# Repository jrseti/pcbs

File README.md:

# Printed Curcuit Board Projects

This repository contains various printed circuit board projects. Also includes any custom firmware where applicable.

## parts

This is a git submodule pointing to https://github.com/jrseti/parts.

The contains pcb related symbols, footprints and 3d files for KiCad PCB projects. All KiCAD projects in this repository will use parts that are in these libraries. 

During development if a part is not in this library, add it. See directions in the parts/READM.md file.

Make sure it is always updated to the latest:

- git submodule update --init --recursive

# mcu_test_board

This is a PCB project to create a board that has a STM32 MCU that runs a PID loop. Once this is debugged and working the design will be inproved in a more encompaing board.

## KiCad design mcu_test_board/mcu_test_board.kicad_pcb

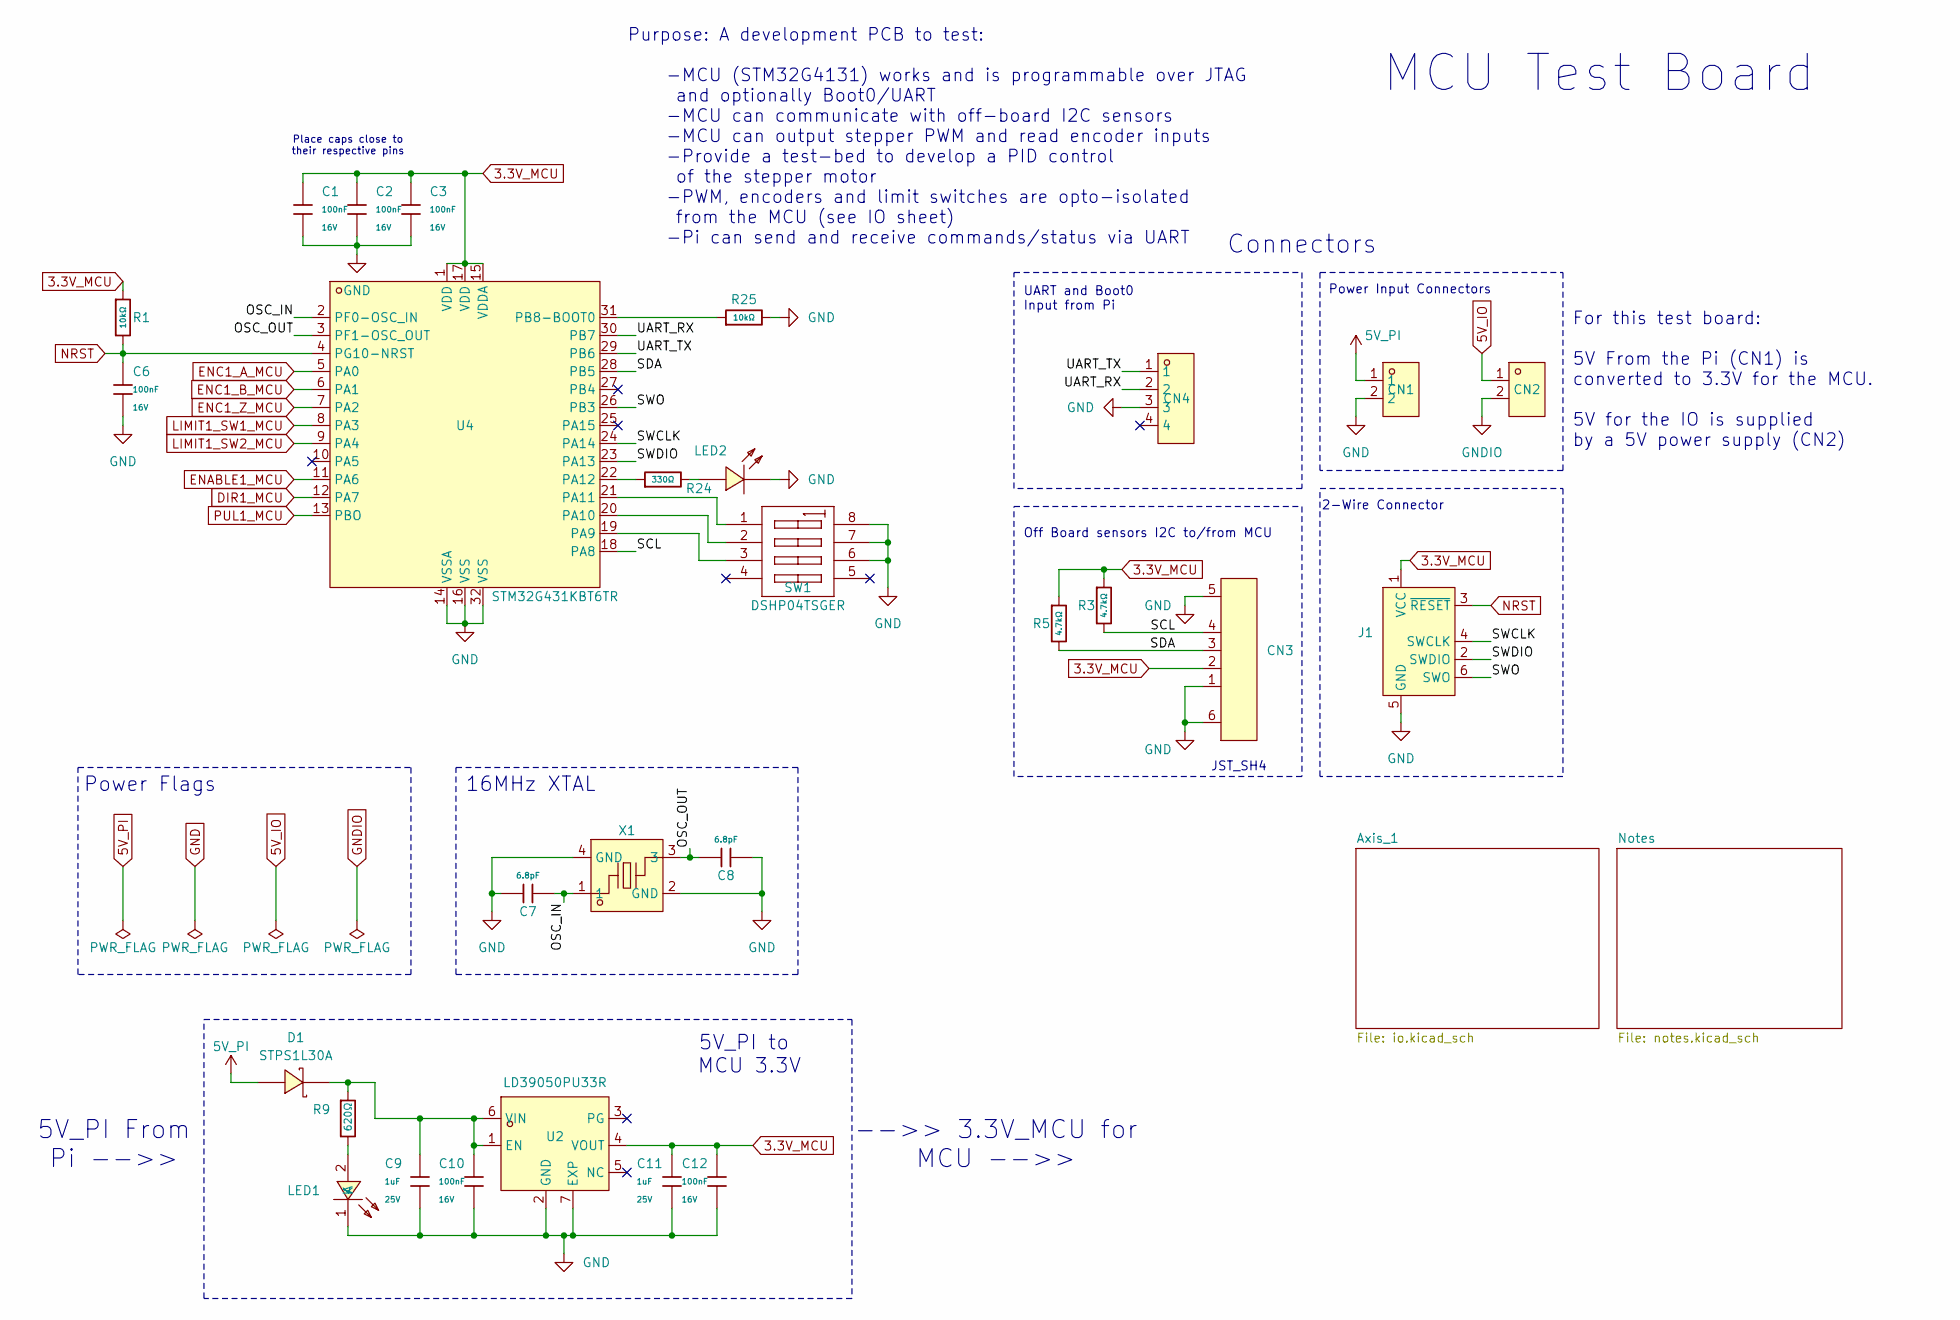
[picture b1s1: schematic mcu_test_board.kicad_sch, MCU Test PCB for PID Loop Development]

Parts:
C1, C2, C3, C6, C10, C12: 100nF; C_0402; Voltage Rated 16V; Tolerance ±10%; Part CL05B104KO5NNNC; LCSC C1525
C7, C8: 6.8pF; C_0402; Voltage Rated 50V; Part 0402CG6R8C500NT; LCSC C1576
C9, C11: 1uF; C_0402; Voltage Rated 25V; Tolerance ±10%; Part CL05A105KA5NQNC; LCSC C52923
CN1, CN2: KF2EDGR-2.54-2P; CONN-TH_P2.54_KF2EDGR-2.54-2P; LCSC Part C577594
CN3: SM04B-SRSS-TB (LF)(SN); CONN-SMD_4P-P1.00_SM04B-SRSS-TB-LF-SN; LCSC Part C160404
CN4: KF2EDGR-2.54-4P; CONN-TH_4P-P2.54_KF2EDGR-2.54-4P; LCSC Part C577596
D1: STPS1L30A; SMA_L4.3-W2.6-LS5.2-RD; LCSC Part C157388
J1: Conn_ARM_SWD_TagConnect_TC2030-NL; Tag-Connect_TC2030-IDC-NL_2x03_P1.27mm_Vertical
LED1, LED2: LTST-S270KGKT; LED-SMD_L1.7-W0.6-RD; LCSC Part C125113
R1, R25: 10kΩ; R_0402; Overload Voltage (Max) 50V; Tolerance ±1%; Part 0402WGF1002TCE; LCSC C25744
R3, R5: 4.7kΩ; R_0402; Overload Voltage (Max) 50V; Tolerance ±1%; Part 0402WGF4701TCE; LCSC C25900
R9: 620Ω; R_0603; Overload Voltage (Max) 75V; Tolerance ±1%; Part 0603WAF6200T5E; LCSC C23220
R24: 330Ω; R_0402; Overload Voltage (Max) 50V; Tolerance ±1%; Part 0402WGF3300TCE; LCSC C25104
SW1: DSHP04TSGER; SW-SMD_8P-L6.7-W5.4-P1.27-LS8.4; LCSC Part C40736
U2: LD39050PU33R; DFN-6_L3.0-W3.0-P0.95-LS3.1-TL-EP; LCSC Part C132827
U4: STM32G431KBT6TR; LQFP-32_L7.0-W7.0-P0.80-LS9.0-BL; LCSC Part C5270317
X1: NX2016SA-16MHZ-EXS00A-CS07826; CRYSTAL-SMD_4P-L2.0-W1.6-BL; LCSC Part C7322371

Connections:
3.3V_MCU: C1.1, C2.1, C3.1, C11.1, C12.1, CN3.2, J1.1 (VCC), R1.1, R3.1, R5.1, U2.4 (VOUT), U4.1 (VDD), U4.15 (VDDA), U4.17 (VDD); also elsewhere on the board
5V_IO: CN2.1; also elsewhere on the board
5V_PI: CN1.1, D1.2 (A)
/OSC_IN: C7.2, U4.2 (PF0-OSC_IN), X1.1
/OSC_OUT: C8.1, U4.3 (PF1-OSC_OUT), X1.3
/SCL: CN3.4, R3.2, U4.18 (PA8)
/SDA: CN3.3, R5.2, U4.28 (PB5)
/SWCLK: J1.4 (SWCLK), U4.24 (PA14)
/SWDIO: J1.2 (SWDIO), U4.23 (PA13)
/SWO: J1.6 (SWO), U4.26 (PB3)
/UART_RX: CN4.2, U4.30 (PB7)
/UART_TX: CN4.1, U4.29 (PB6)
DIR1_MCU: U4.12 (PA7); also elsewhere on the board
ENABLE1_MCU: U4.11 (PA6); also elsewhere on the board
ENC1_A_MCU: U4.5 (PA0); also elsewhere on the board
ENC1_B_MCU: U4.6 (PA1); also elsewhere on the board
ENC1_Z_MCU: U4.7 (PA2); also elsewhere on the board
GND: C1.2, C2.2, C3.2, C6.2, C7.1, C8.2, C9.2, C10.2, C11.2, C12.2, CN1.2, CN3.1, CN3.5, CN3.6, CN4.3, J1.5 (GND), LED1.1 (K), LED2.1 (K), R25.2, SW1.6 (B3), SW1.7 (B2), SW1.8 (B1), U2.2 (GND), U2.7 (EXP), U4.14 (VSSA), U4.16 (VSS), U4.32 (VSS), X1.2 (GND), X1.4 (GND); also elsewhere on the board
GNDIO: CN2.2; also elsewhere on the board
LIMIT1_SW1_MCU: U4.8 (PA3); also elsewhere on the board
LIMIT1_SW2_MCU: U4.9 (PA4); also elsewhere on the board
NRST: C6.1, J1.3 (~RESET), R1.2, U4.4 (PG10-NRST)
unnamed: C9.1, C10.1, D1.1 (C), R9.1, U2.1 (EN), U2.6 (VIN)
unnamed: LED1.2 (A), R9.2
unnamed: LED2.2 (A), R24.2
unnamed: SW1.1 (A1), U4.21 (PA11)
unnamed: SW1.2 (A2), U4.20 (PA10)
unnamed: SW1.3 (A3), U4.19 (PA9)
unnamed: R24.1, U4.22 (PA12)
unnamed: R25.1, U4.31 (PB8-BOOT0)
PUL1_MCU: U4.13 (PBO); also elsewhere on the board

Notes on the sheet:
2-Wire Connector
16MHz XTAL
Off Board sensors I2C to/from MCU
Connectors
JST_SH4
Power Input Connectors
UART and Boot0 Input from Pi
For this test board: 5V From the Pi (CN1) is converted to 3.3V for the MCU. 5V for the IO is supplied by a 5V power supply (CN2)
Place caps close to their respective pins
Power Flags
-->> 3.3V_MCU for MCU -->>
MCU Test Board
Purpose: A development PCB to test: -MCU (STM32G4131) works and is programmable over JTAG and optionally Boot0/UART -MCU can communicate with off-board I2C sensors -MCU can output stepper PWM and read encoder inputs -Provide a test-bed to develop a PID control of the stepper motor -PWM, encoders an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
5V_PI to MCU 3.3V
5V_PI From Pi -->>

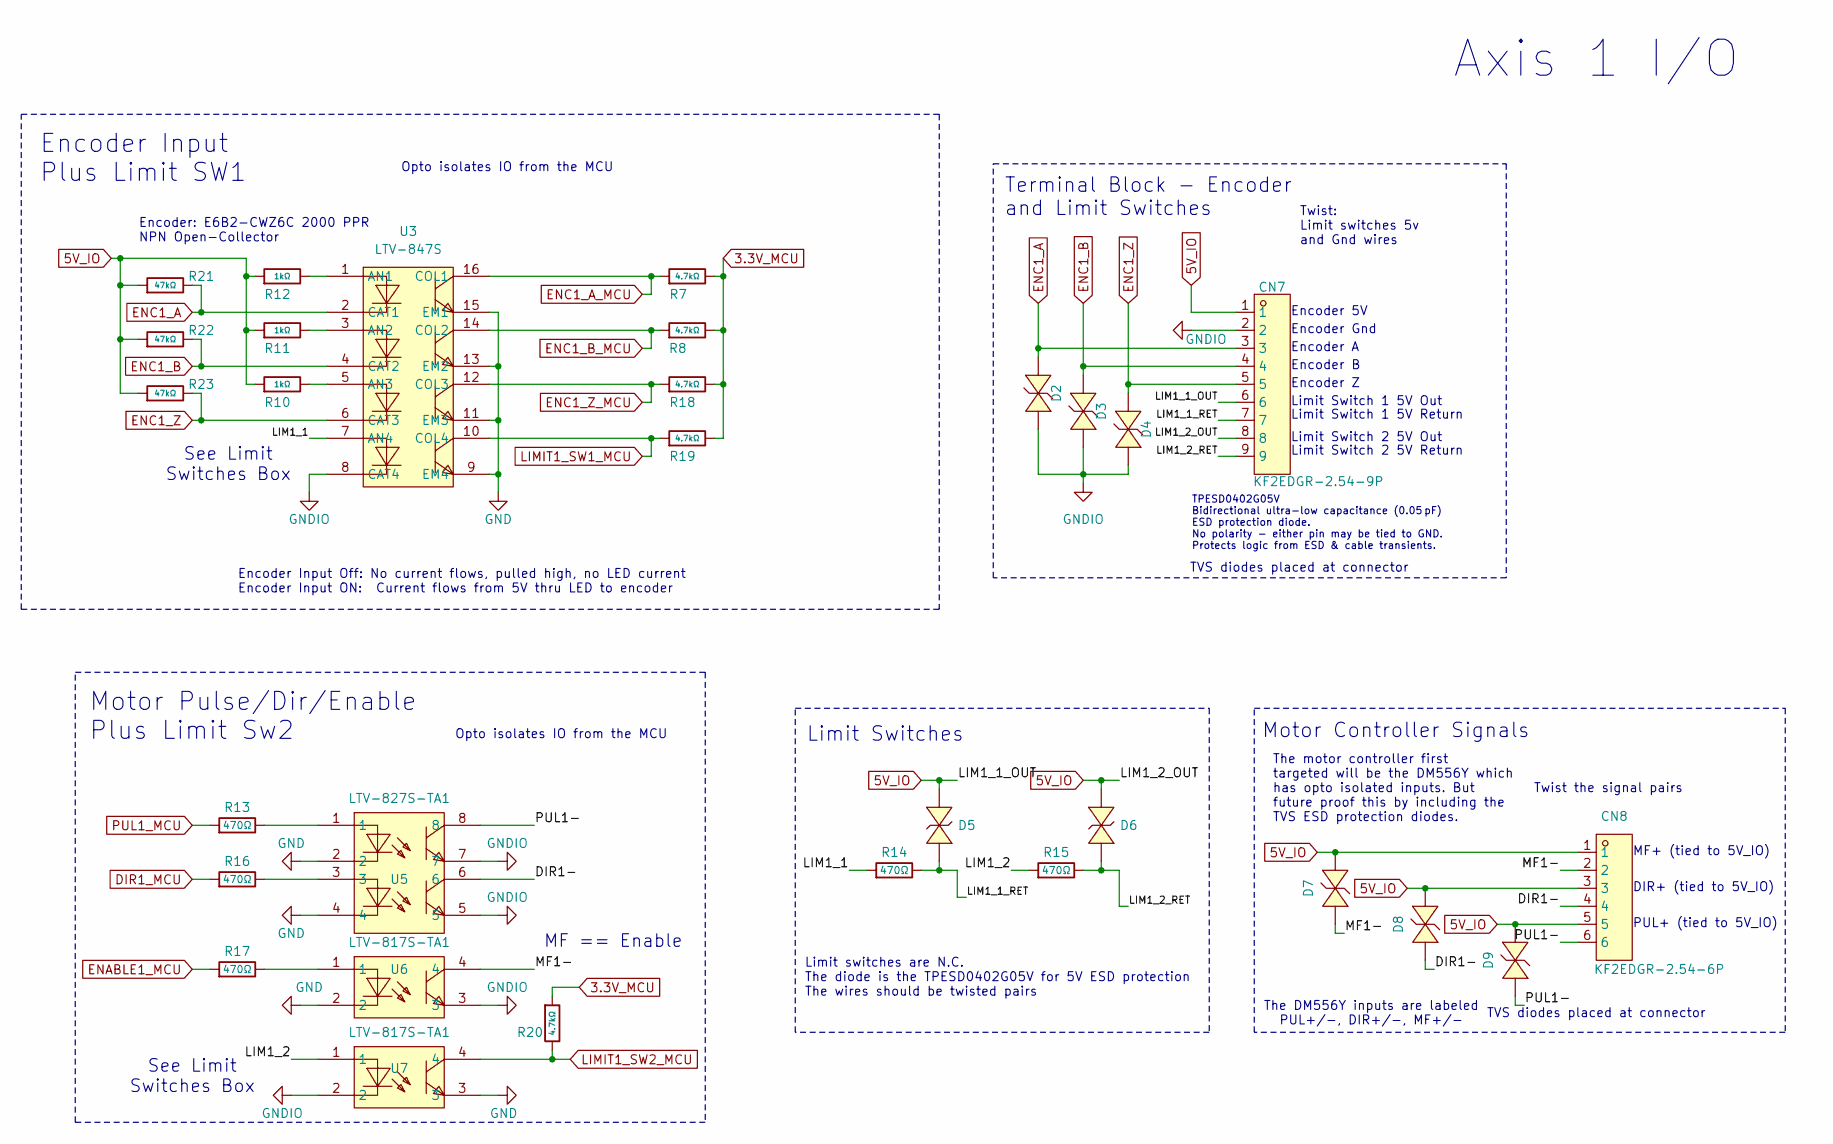
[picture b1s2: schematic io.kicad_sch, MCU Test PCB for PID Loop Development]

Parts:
CN7: KF2EDGR-2.54-9P; CONN-TH_9P-P2.54_KF2EDGR-2.54-9P; LCSC Part C577601
CN8: KF2EDGR-2.54-6P; CONN-TH_KF2EDGR-2.54-6P; LCSC Part C577598
D2, D3, D4, D7, D8, D9: TPESD0402G05V; D0402-BI; LCSC Part C558615
D5, D6: TPESD0402G05V; D0402-BI; LCSC Part C558617
R7, R8, R18, R19, R20: 4.7kΩ; R_0603; Overload Voltage (Max) 75V; Tolerance ±1%; Part 0603WAF4701T5E; LCSC C23162
R10, R11, R12: 1kΩ; R_0402; Overload Voltage (Max) 50V; Tolerance ±1%; Part 0402WGF1001TCE; LCSC C11702
R13, R14, R15, R16, R17: 470Ω; R_0402; Overload Voltage (Max) 50V; Tolerance ±1%; Part 0402WGF4700TCE; LCSC C25117
R21, R22, R23: 47kΩ; R_0402; Overload Voltage (Max) 50V; Tolerance ±1%; Part 0402WGF4702TCE; LCSC C25792
U3: LTV-847S; SMD-16_L20.0-W6.5-P2.54-LS10.2-BL; LCSC Part C114599
U5: LTV-827S-TA1; SMD-8_L9.8-W6.6-P2.54-LS10.3-BL; LCSC Part C22112
U6, U7: LTV-817S-TA1; OPTO-SMD-4_L4.6-W6.5-P2.54-LS10.3-BL; LCSC Part C125121

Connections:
3.3V_MCU: R7.2, R8.2, R18.2, R19.2, R20.1; also elsewhere on the board
5V_IO: CN7.1, CN7.6, CN7.8, CN8.1, CN8.3, CN8.5, D5.1, D6.1, D7.1 (K), D8.1 (K), D9.1 (K), R10.1, R11.1, R12.1, R21.1, R22.1, R23.1; also elsewhere on the board
/Axis_1/DIR1-: CN8.4, D8.2 (A), U5.6
/Axis_1/LIM1_1: R14.1, U3.7 (AN4)
/Axis_1/LIM1_1_RET: CN7.7, D5.2, R14.2
/Axis_1/LIM1_2: R15.1, U7.1
/Axis_1/LIM1_2_RET: CN7.9, D6.2, R15.2
/Axis_1/MF1-: CN8.2, D7.2 (A), U6.4
/Axis_1/PUL1-: CN8.6, D9.2 (A), U5.8
DIR1_MCU: R16.1; also elsewhere on the board
ENABLE1_MCU: R17.1; also elsewhere on the board
ENC1_A: CN7.3, D2.1 (K), R21.2, U3.2 (CAT1)
ENC1_A_MCU: R7.1, U3.16 (COL1); also elsewhere on the board
ENC1_B: CN7.4, D3.1 (K), R22.2, U3.4 (CAT2)
ENC1_B_MCU: R8.1, U3.14 (COL2); also elsewhere on the board
ENC1_Z: CN7.5, D4.1 (K), R23.2, U3.6 (CAT3)
ENC1_Z_MCU: R18.1, U3.12 (COL3); also elsewhere on the board
GND: U3.9 (EM4), U3.11 (EM3), U3.13 (EM2), U3.15 (EM1), U5.2, U5.4, U6.2, U7.3; also elsewhere on the board
GNDIO: CN7.2, D2.2 (A), D3.2 (A), D4.2 (A), U3.8 (CAT4), U5.5, U5.7, U6.3, U7.2; also elsewhere on the board
LIMIT1_SW1_MCU: R19.1, U3.10 (COL4); also elsewhere on the board
LIMIT1_SW2_MCU: R20.2, U7.4; also elsewhere on the board
unnamed: R13.2, U5.1
unnamed: R16.2, U5.3
unnamed: R17.2, U6.1
unnamed: R12.2, U3.1 (AN1)
unnamed: R11.2, U3.3 (AN2)
unnamed: R10.2, U3.5 (AN3)
PUL1_MCU: R13.1; also elsewhere on the board

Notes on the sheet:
Limit Switch 2 5V Return
Encoder A
Limit switches are N.C. The diode is the TPESD0402G05V for 5V ESD protection The wires should be twisted pairs
PUL+ (tied to 5V_IO)
Opto isolates IO from the MCU
Encoder 5V
Motor Pulse/Dir/Enable Plus Limit Sw2
See Limit Switches Box
Encoder: E6B2-CWZ6C 2000 PPR NPN Open-Collector
Opto isolates IO from the MCU
Encoder Gnd
Axis 1 I/O
Twist: Limit switches 5v and Gnd wires
TPESD0402G05V Bidirectional ultra-low capacitance (0.05 pF) ESD protection diode. No polarity - either pin may be tied to GND. Protects logic from ESD & cable transients.
Limit Switch 2 5V Out
Encoder Input Off: No current flows, pulled high, no LED current Encoder Input ON: Current flows from 5V thru LED to encoder
TVS diodes placed at connector
MF+ (tied to 5V_IO)
Limit Switch 1 5V Return
Terminal Block - Encoder and Limit Switches
The DM556Y inputs are labeled PUL+/-, DIR+/-, MF+/-
Encoder Input Plus Limit SW1
Limit Switches
Motor Controller Signals
Encoder Z
DIR+ (tied to 5V_IO)
The motor controller first targeted will be the DM556Y which has opto isolated inputs. But future proof this by including the TVS ESD protection diodes.
Twist the signal pairs
MF == Enable
Limit Switch 1 5V Out
Encoder B

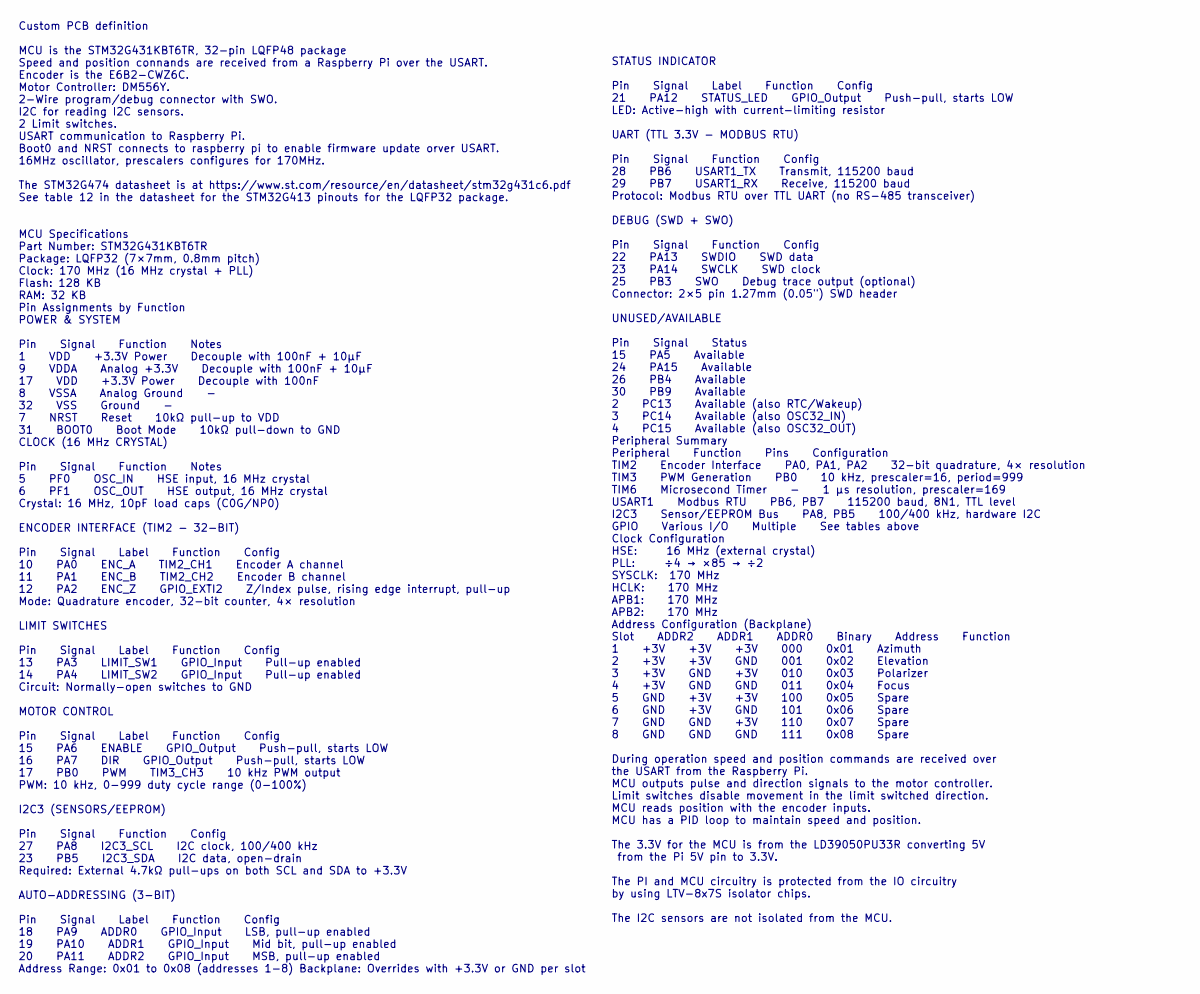
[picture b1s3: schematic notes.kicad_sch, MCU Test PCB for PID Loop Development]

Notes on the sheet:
STATUS INDICATOR Pin Signal Label Function Config 21 PA12 STATUS_LED GPIO_Output Push-pull, starts LOW LED: Active-high with current-limiting resistor UART (TTL 3.3V - MODBUS RTU) Pin Signal Function Config 28 PB6 USART1_TX Transmit, 115200 baud 29 PB7 USART1_RX Receive, 115200 baud Protocol: Modbu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
Custom PCB definition MCU is the STM32G431KBT6TR, 32-pin LQFP48 package Speed and position connands are received from a Raspberry Pi over the USART. Encoder is the E6B2-CWZ6C. Motor Controller: DM556Y. 2-Wire program/debug connector with SWO. I2C for reading I2C sensors. 2 Limit switches. USART com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

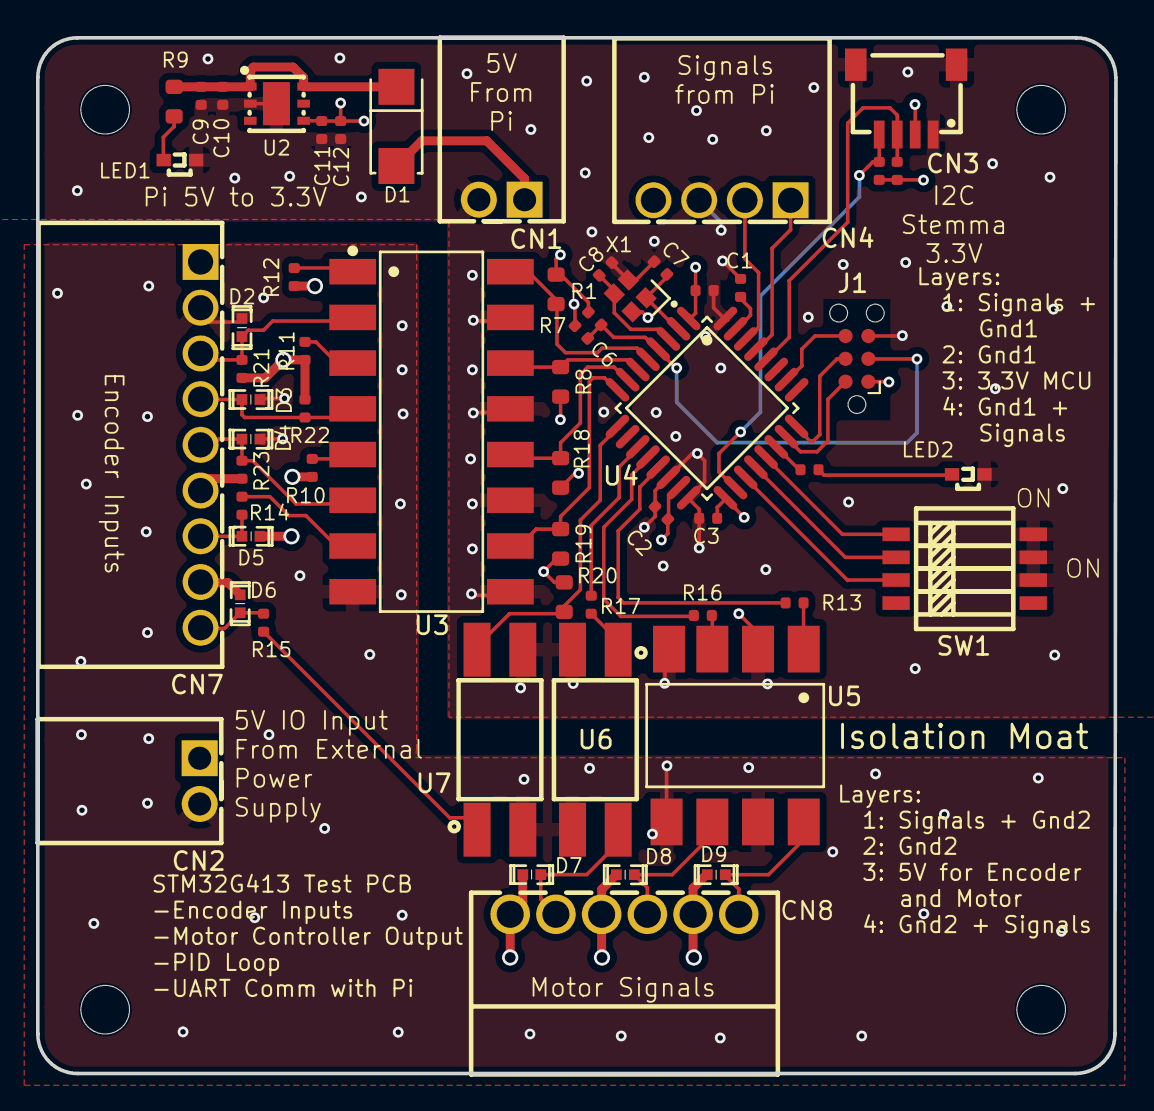
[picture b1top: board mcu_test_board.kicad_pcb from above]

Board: 4 copper layers, 59.9 x 57.5 mm, 62 parts (0 on the bottom side), 47 nets.

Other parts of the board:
M1, M1#2, M1#3, M1#4: MountingHole_2.7mm_M2.5_ISO14580

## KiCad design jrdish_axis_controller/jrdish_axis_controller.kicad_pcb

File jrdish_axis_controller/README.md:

# Axis Controller

This PCB is an improved version of the mcu_test_board PCB. RS485, better isolation, fan power output and mode.

## Overview

This board follows on from the mcu_test_board. The mcu_test_board functions well, but quickly necessary improvements became evident to be able to fully service one axis of the satellite dish.

- PWM output. Isolated.
- Encoder inputs. Isolated.
- MCU will execute a PID loop.
- Upgrade to the STM32G473CET6 LQFP48. Has 512KB Flash vs 128KB.
- RS485. Isolated. With passthrough.
- MCU controllerd 12V output for fan on/off. Isolated.
- Requires only 12V input
- I2C isolation
- Onboard I2C temperature/humidity sensor. Not isolated.
- EEPROM.

## MCU

STM32G474CET6

- 512KB flash
- As of April 9, 2026 JLCPCB has 1152 in stock
- 48 pin
- JLCPCB Part # C730125 - https://jlcpcb.com/partdetail/STMicroelectronics-STM32G474CET6/C730125
- Datasheet: https://www.lcsc.com/datasheet/C730125.pdf

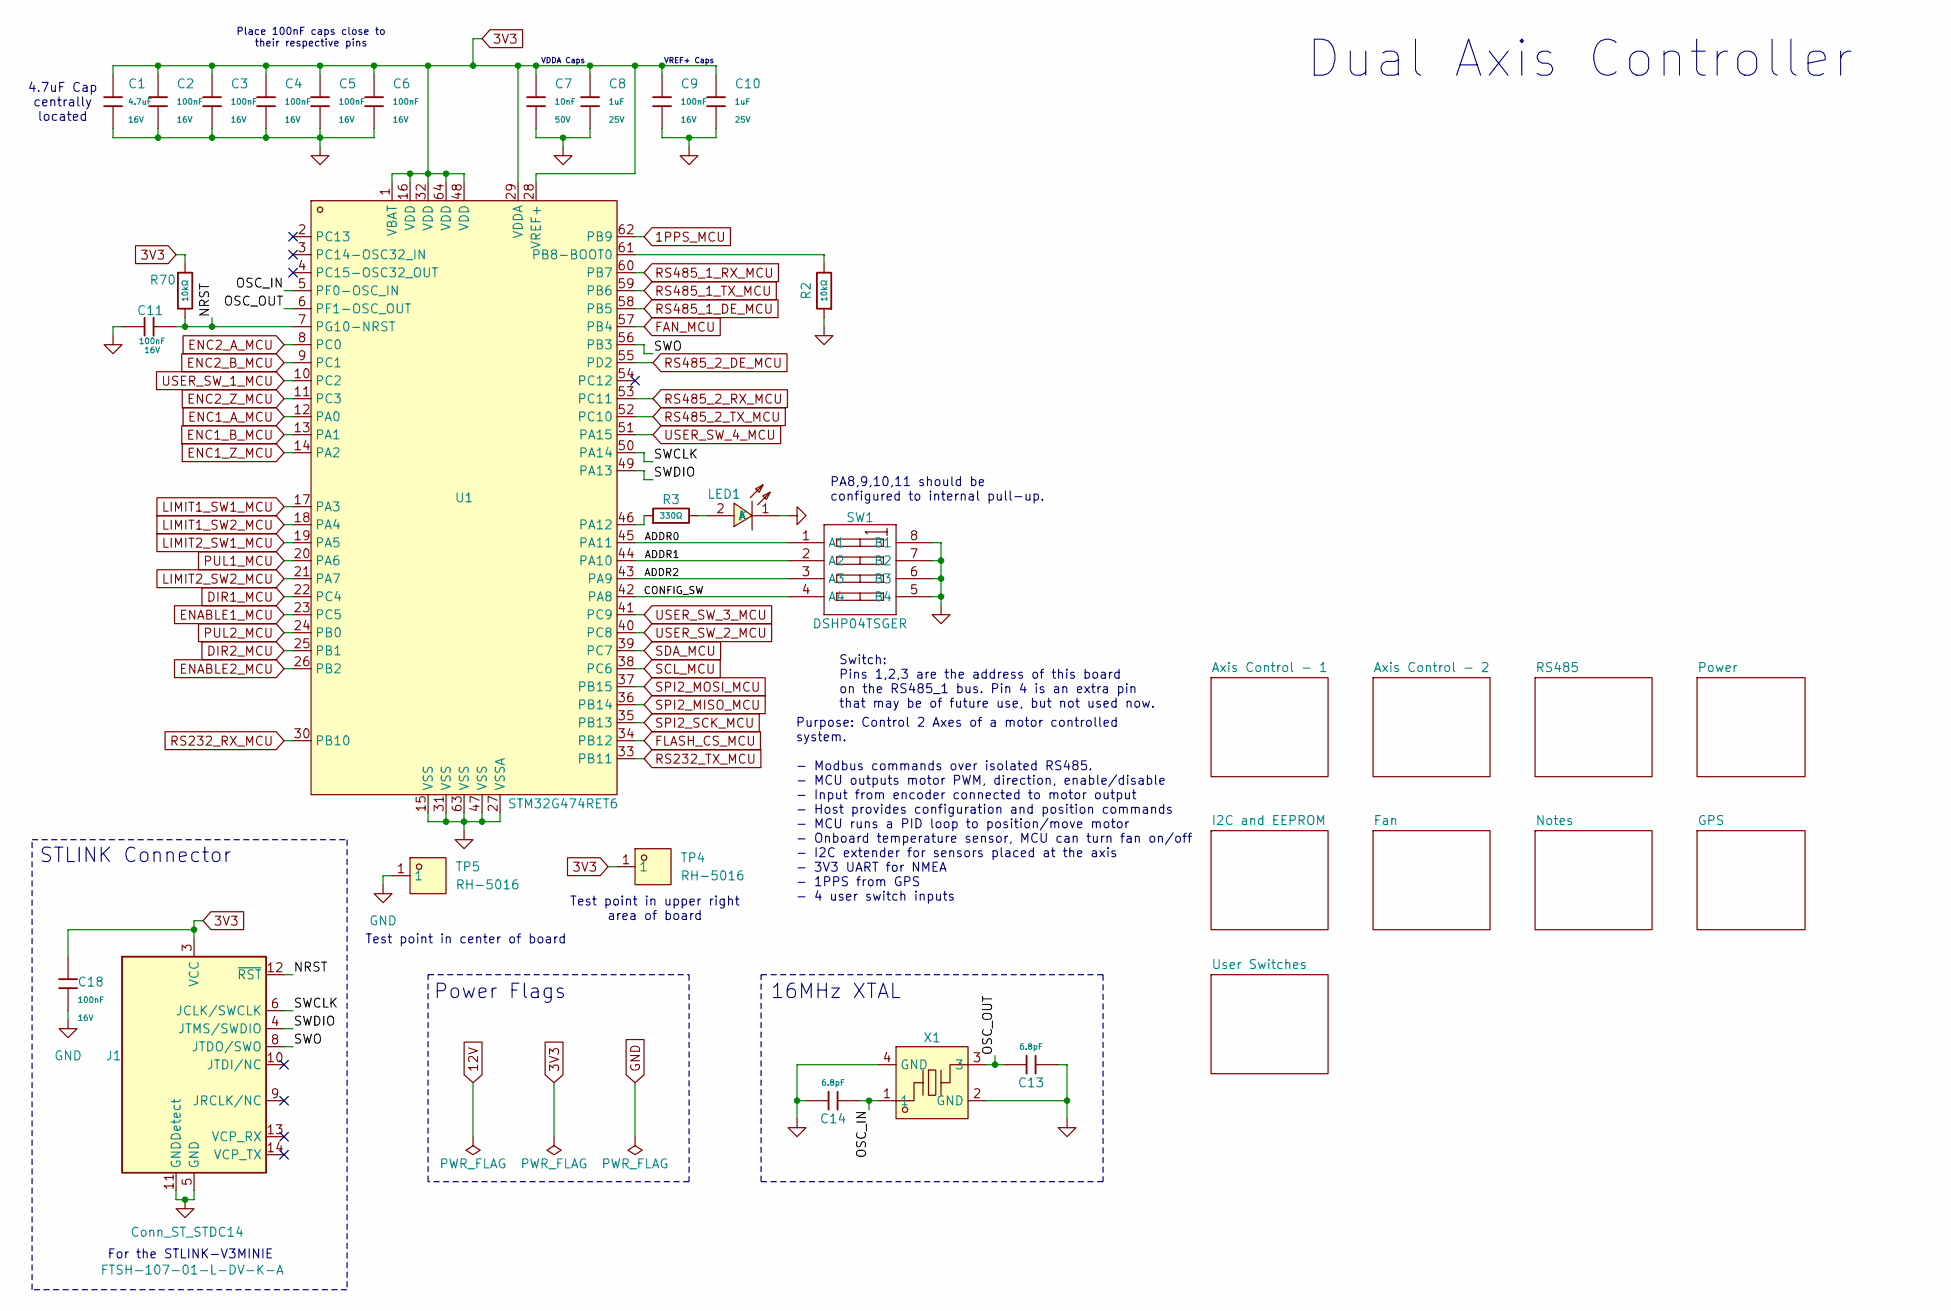
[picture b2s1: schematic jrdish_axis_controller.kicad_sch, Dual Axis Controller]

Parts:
C1: 4.7uF; C_0603; Voltage Rated 16V; Tolerance ±10%; Part CL10A475KO8NNNC; LCSC C19666
C2, C3, C4, C5, C6, C9, C11, C18: 100nF; C_0402; Voltage Rated 16V; Tolerance ±10%; Part CL05B104KO5NNNC; LCSC C1525
C7: 10nF; C_0402; Voltage Rated 50V; Tolerance ±10%; Part CL05B103KB5NNNC; LCSC C15195
C8, C10: 1uF; C_0402; Voltage Rated 25V; Tolerance ±10%; Part CL05A105KA5NQNC; LCSC C52923
C13, C14: 6.8pF; C_0402; Voltage Rated 50V; Part 0402CG6R8C500NT; LCSC C1576
J1: Conn_ST_STDC14; HDR-SMD_14P-P1.27_FTSH-107-01-L-DV-K; LCSC C5563894
LED1: LTST-S270KGKT; LED-SMD_L1.7-W0.6-RD; LCSC Part C125113
R2, R70: 10kΩ; R_0402; Overload Voltage (Max) 50V; Tolerance ±1%; Part 0402WGF1002TCE; LCSC C173683
R3: 330Ω; R_0402; Overload Voltage (Max) 50V; Tolerance ±1%; Part 0402WGF3300TCE; LCSC C25104
SW1: DSHP04TSGER; SW-SMD_8P-L6.7-W5.4-P1.27-LS8.4; LCSC Part C40736
TP4, TP5: RH-5016; TESTPOINT-SMD_L3.0-W2.0; MPN RH-5016; LCSC Part C5199799
U1: STM32G474RET6; LQFP-64_L10.0-W10.0-P0.50-LS12.0-BL; MPN STM32G474RET6; LCSC Part C521608
X1: NX2016SA-16MHZ-EXS00A-CS07826; CRYSTAL-SMD_4P-L2.0-W1.6-BL; LCSC Part C7322371

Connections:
1PPS_MCU: U1.62 (PB9); also elsewhere on the board
/ADDR0: SW1.1 (A1), U1.45 (PA11)
/ADDR1: SW1.2 (A2), U1.44 (PA10)
/ADDR2: SW1.3 (A3), U1.43 (PA9)
/CONFIG_SW: SW1.4 (A4), U1.42 (PA8)
/NRST: C11.1, J1.12 (~RST), R70.2, U1.7 (PG10-NRST)
/OSC_IN: C14.2, U1.5 (PF0-OSC_IN), X1.1
/OSC_OUT: C13.1, U1.6 (PF1-OSC_OUT), X1.3
/SWCLK: J1.6 (JCLK/SWCLK), U1.50 (PA14)
/SWDIO: J1.4 (JTMS/SWDIO), U1.49 (PA13)
/SWO: J1.8 (JTDO/SWO), U1.56 (PB3)
DIR1_MCU: U1.22 (PC4); also elsewhere on the board
DIR2_MCU: U1.25 (PB1); also elsewhere on the board
ENABLE1_MCU: U1.23 (PC5); also elsewhere on the board
ENABLE2_MCU: U1.26 (PB2); also elsewhere on the board
ENC1_A_MCU: U1.12 (PA0); also elsewhere on the board
ENC1_B_MCU: U1.13 (PA1); also elsewhere on the board
ENC1_Z_MCU: U1.14 (PA2); also elsewhere on the board
ENC2_A_MCU: U1.8 (PC0); also elsewhere on the board
ENC2_B_MCU: U1.9 (PC1); also elsewhere on the board
ENC2_Z_MCU: U1.11 (PC3); also elsewhere on the board
FAN_MCU: U1.57 (PB4); also elsewhere on the board
FLASH_CS_MCU: U1.34 (PB12); also elsewhere on the board
GND: C1.2, C2.2, C3.2, C4.2, C5.2, C6.2, C7.2, C8.2, C9.2, C10.2, C11.2, C13.2, C14.1, C18.2, J1.5 (GND), J1.7 (GND), J1.11 (GNDDetect), LED1.1 (K), R2.1, SW1.5 (B4), SW1.6 (B3), SW1.7 (B2), SW1.8 (B1), TP5.1 (1_1), U1.15 (VSS), U1.27 (VSSA), U1.31 (VSS), U1.47 (VSS), U1.63 (VSS), X1.2 (GND), X1.4 (GND); also elsewhere on the board
LIMIT1_SW1_MCU: U1.17 (PA3); also elsewhere on the board
LIMIT1_SW2_MCU: U1.18 (PA4); also elsewhere on the board
LIMIT2_SW1_MCU: U1.19 (PA5); also elsewhere on the board
LIMIT2_SW2_MCU: U1.21 (PA7); also elsewhere on the board
unnamed: LED1.2 (A), R3.2
unnamed: R3.1, U1.46 (PA12)
unnamed: R2.2, U1.61 (PB8-BOOT0)
PUL1_MCU: U1.20 (PA6); also elsewhere on the board
PUL2_MCU: U1.24 (PB0); also elsewhere on the board
RS232_RX_MCU: U1.30 (PB10); also elsewhere on the board
RS232_TX_MCU: U1.33 (PB11); also elsewhere on the board
RS485_1_DE_MCU: U1.58 (PB5); also elsewhere on the board
RS485_1_RX_MCU: U1.60 (PB7); also elsewhere on the board
RS485_1_TX_MCU: U1.59 (PB6); also elsewhere on the board
RS485_2_DE_MCU: U1.55 (PD2); also elsewhere on the board
RS485_2_RX_MCU: U1.53 (PC11); also elsewhere on the board
RS485_2_TX_MCU: U1.52 (PC10); also elsewhere on the board
SCL_MCU: U1.38 (PC6); also elsewhere on the board
SDA_MCU: U1.39 (PC7); also elsewhere on the board
SPI2_MISO_MCU: U1.36 (PB14); also elsewhere on the board
SPI2_MOSI_MCU: U1.37 (PB15); also elsewhere on the board
SPI2_SCK_MCU: U1.35 (PB13); also elsewhere on the board
USER_SW_1_MCU: U1.10 (PC2); also elsewhere on the board
USER_SW_2_MCU: U1.40 (PC8); also elsewhere on the board
USER_SW_3_MCU: U1.41 (PC9); also elsewhere on the board
USER_SW_4_MCU: U1.51 (PA15); also elsewhere on the board

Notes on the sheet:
Purpose: Control 2 Axes of a motor controlled system. - Modbus commands over isolated RS485. - MCU outputs motor PWM, direction, enable/disable - Input from encoder connected to motor output - Host provides configuration and position commands - MCU runs a PID loop to position/move motor - Onboard t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
Switch: Pins 1,2,3 are the address of this board on the RS485_1 bus. Pin 4 is an extra pin that may be of future use, but not used now.
Place 100nF caps close to their respective pins
Power Flags
For the STLINK-V3MINIE
PA8,9,10,11 should be configured to internal pull-up.
16MHz XTAL
VREF+ Caps
Test point in upper right area of board
Test point in center of board
Dual Axis Controller
VDDA Caps
4.7uF Cap centrally located
STLINK Connector

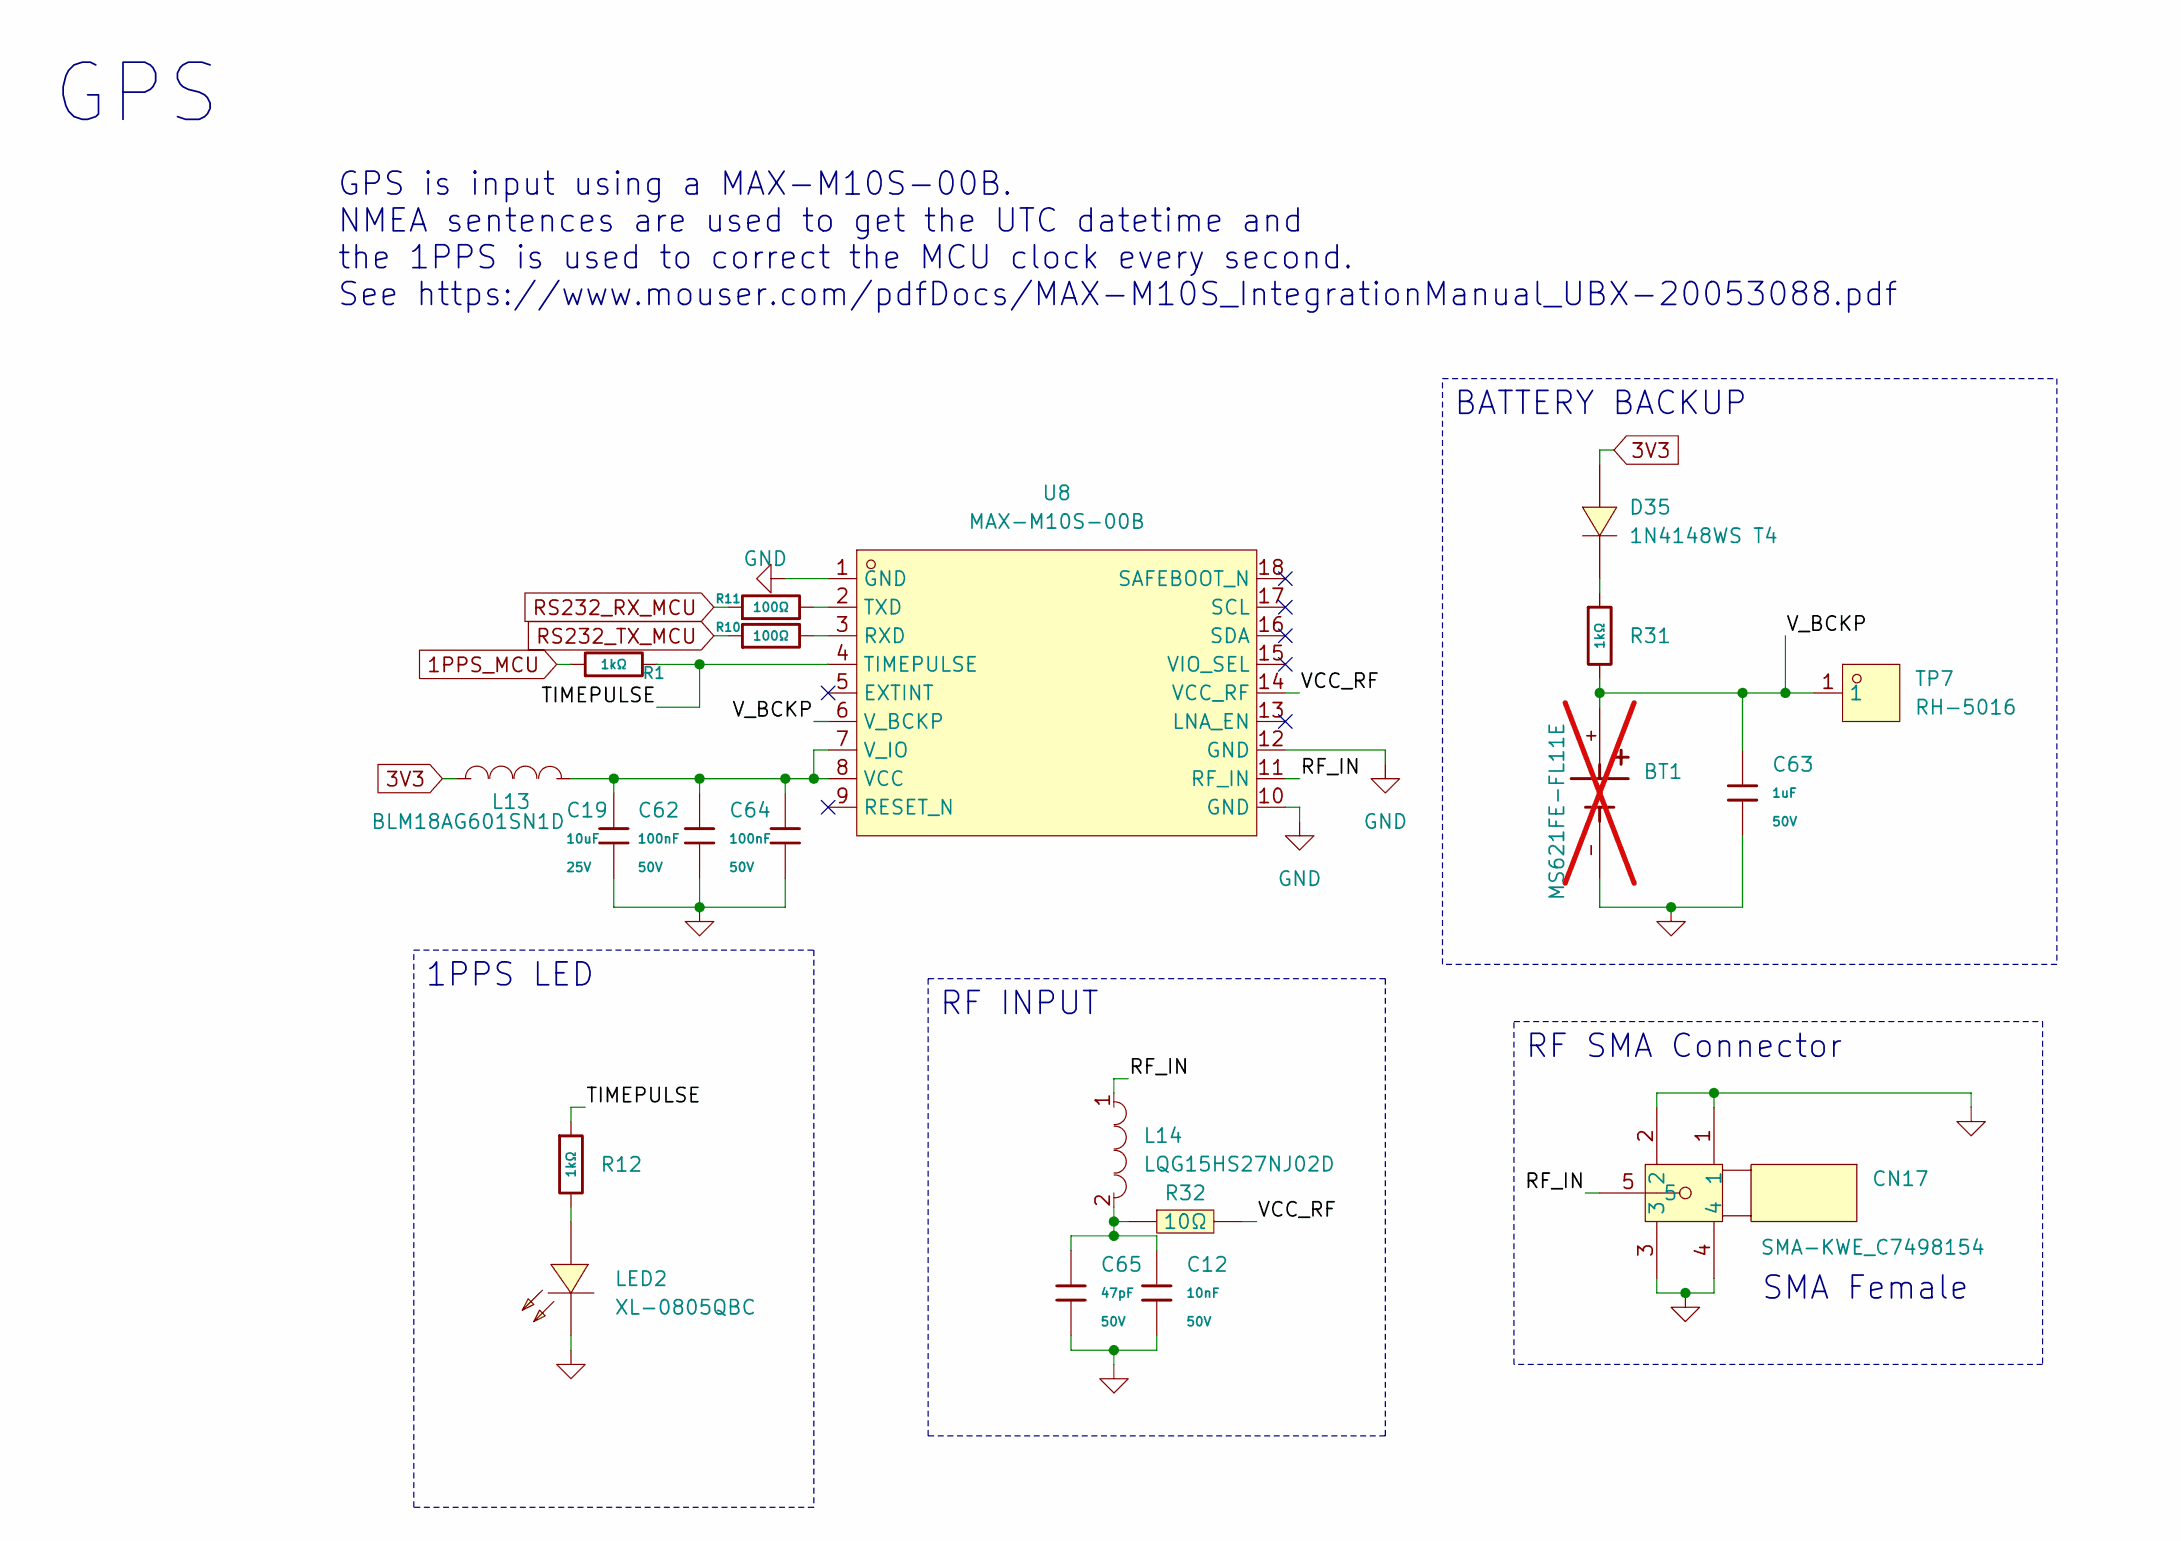
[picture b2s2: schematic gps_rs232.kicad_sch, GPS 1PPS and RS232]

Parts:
BT1: MS621FE-FL11E; BAT_MS621FE-FL11E; PARTREV E; not fitted
C12: 10nF; C_0603; Voltage Rated 50V; Tolerance ±10%; Part 0603B103K500NT; LCSC C57112
C19: 10uF; C_0603; Voltage Rated 25V; Tolerance ±20%; Part CL10A106MA8NRNC; LCSC C96446
C62, C64: 100nF; C_0603; Voltage Rated 50V; Tolerance ±10%; Part CC0603KRX7R9BB104; LCSC C14663
C63: 1uF; C_0603; Voltage Rated 50V; Tolerance ±10%; Part CL10A105KB8NNNC; LCSC C15849
C65: 47pF; C_0603; Voltage Rated 50V; Tolerance ±5%; Part CL10C470JB8NNNC; LCSC C1671
CN17: SMA-KWE_C7498154; SMA-TH_SMA-KWE_C7498154; MPN SMA-KWE; LCSC Part C7498154
D35: 1N4148WS T4; SOD-323_L1.8-W1.3-LS2.5-RD; MPN 1N4148WS; LCSC Part C2128
L13: BLM18AG601SN1D; L0603; MPN BLM18AG601SN1D; LCSC Part C19330
L14: LQG15HS27NJ02D; L0402-RD; MPN LQG15HS27NJ02D; LCSC Part C12669
LED2: XL-0805QBC; LED0805-R-RD; MPN KT-0805B; LCSC Part C2293
R1: 1kΩ; R_0402; Overload Voltage (Max) 50V; Tolerance ±1%; Part 0402WGF1001TCE; LCSC C11702
R10, R11: 100Ω; R_0402; Overload Voltage (Max) 50V; Tolerance ±1%; Part 0402WGF1000TCE; LCSC C25076
R12, R31: 1kΩ; R_0603; Overload Voltage (Max) 75V; Tolerance ±1%; Part 0603WAF1001T5E; LCSC C21190
R32: 10Ω; R1206; MPN 1206W4F100JT5E; LCSC Part C17903
TP7: RH-5016; TESTPOINT-SMD_L3.0-W2.0; MPN RH-5016; LCSC Part C5199799
U8: MAX-M10S-00B; SMD-18_L10.1-W9.7-P1.10-TL_SKG09F; MPN MAX-M10S-00B; LCSC Part C4153167

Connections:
1PPS_MCU: R1.1; also elsewhere on the board
/GPS/RF_IN: CN17.5, L14.1, U8.11 (RF_IN)
/GPS/TIMEPULSE: R1.2, R12.1, U8.4 (TIMEPULSE)
/GPS/VCC_RF: R32.2, U8.14 (VCC_RF)
/GPS/V_BCKP: BT1.+, C63.1, R31.2, TP7.1 (1_1), U8.6 (V_BCKP)
GND: BT1.-, C12.2, C19.2, C62.2, C63.2, C64.2, C65.2, CN17.1, CN17.2, CN17.3, CN17.4, LED2.2 (K), U8.1 (GND), U8.10 (GND), U8.12 (GND); also elsewhere on the board
unnamed: D35.1 (K), R31.1
unnamed: LED2.1 (A), R12.2
unnamed: R10.2, U8.3 (RXD)
unnamed: R11.2, U8.2 (TXD)
unnamed: C19.1, C62.1, C64.1, L13.2, U8.7 (V_IO), U8.8 (VCC)
RS232_RX_MCU: R11.1; also elsewhere on the board
RS232_TX_MCU: R10.1; also elsewhere on the board

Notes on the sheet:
GPS
GPS is input using a MAX-M10S-00B. NMEA sentences are used to get the UTC datetime and the 1PPS is used to correct the MCU clock every second. See https://www.mouser.com/pdfDocs/MAX-M10S_IntegrationManual_UBX-20053088.pdf
SMA Female
RF SMA Connector
1PPS LED
RF INPUT
BATTERY BACKUP
